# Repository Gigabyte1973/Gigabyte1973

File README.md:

# Gigabyte1973
BMS with RS485 comunication

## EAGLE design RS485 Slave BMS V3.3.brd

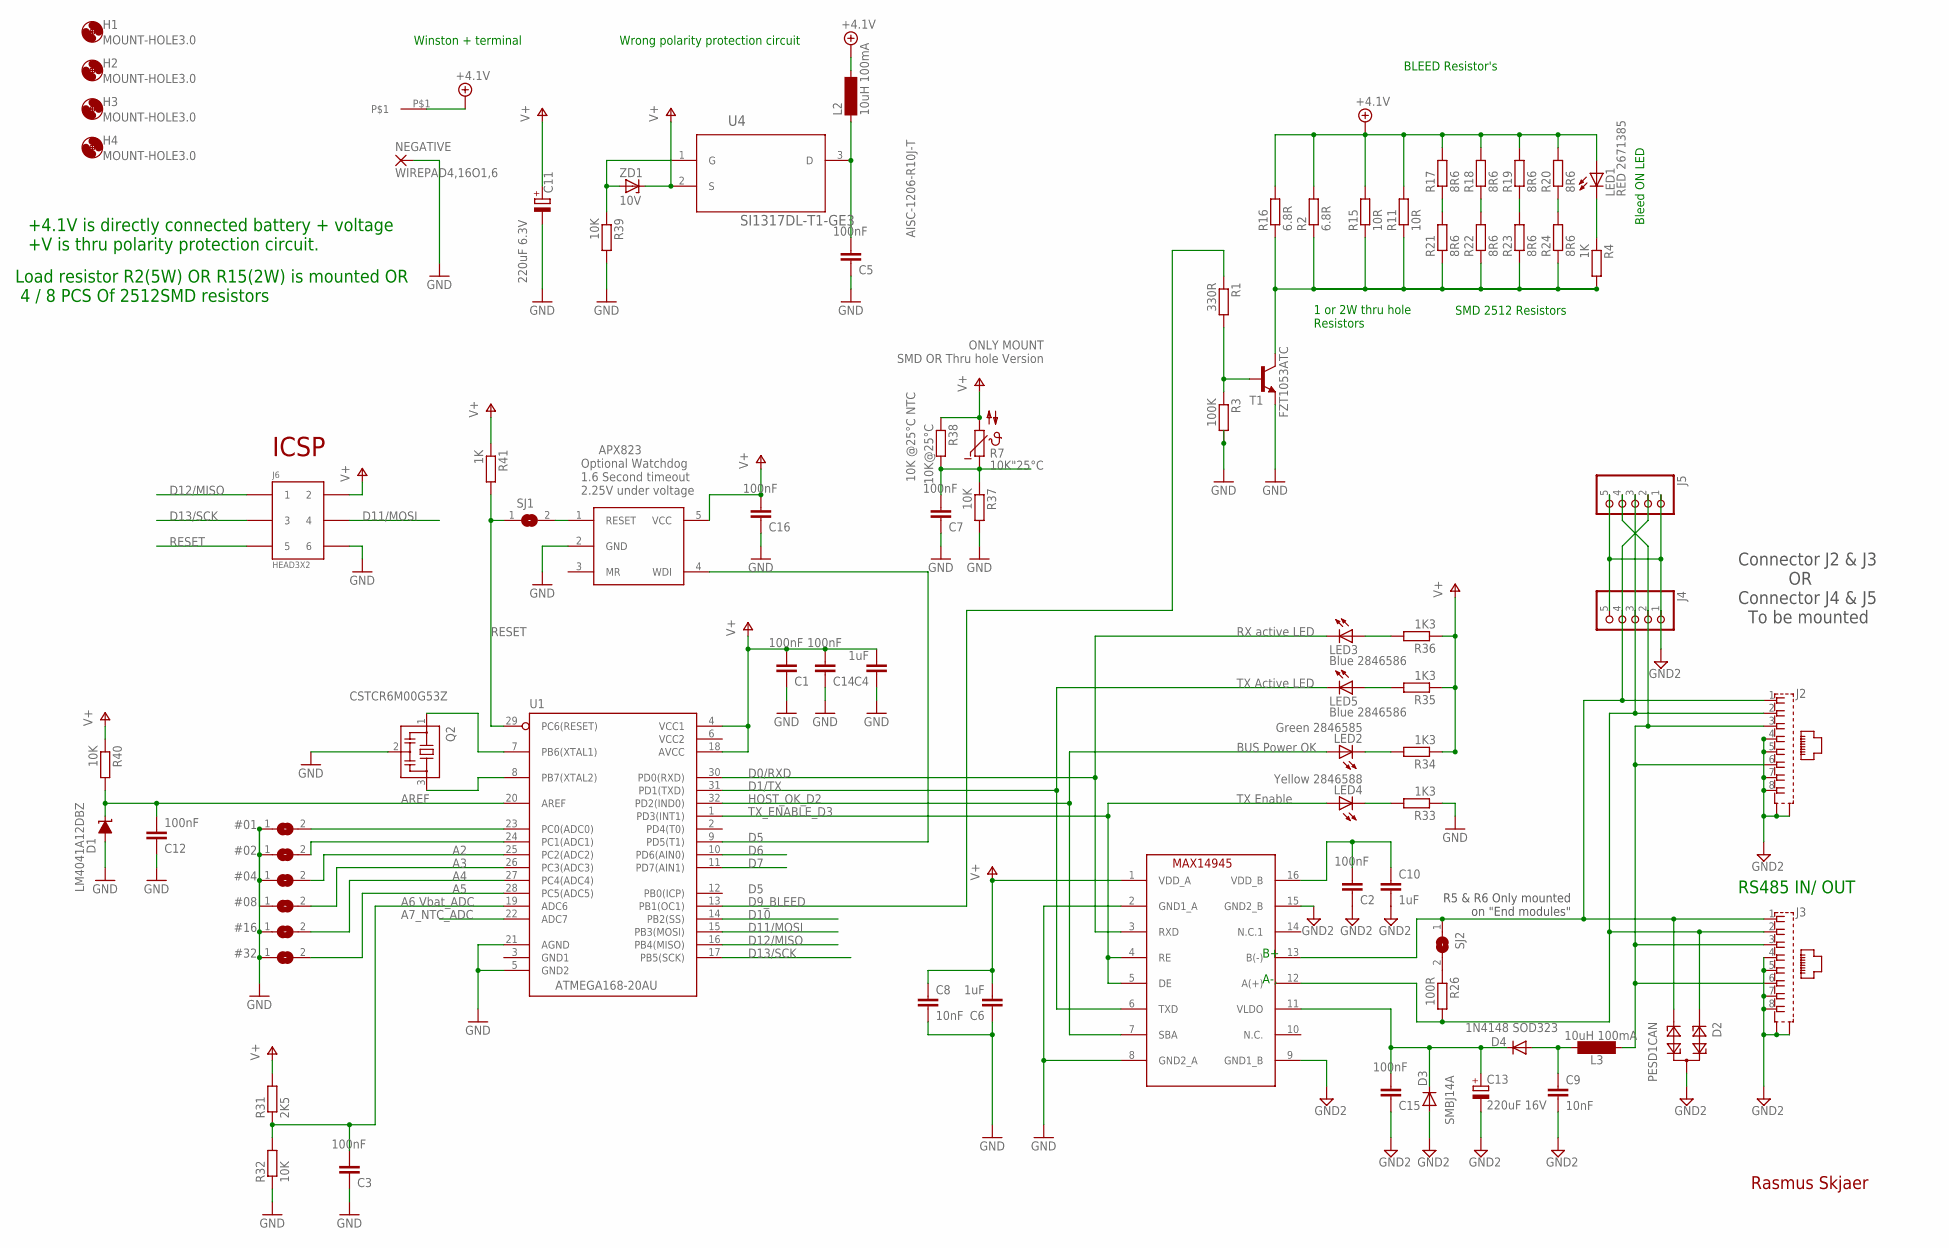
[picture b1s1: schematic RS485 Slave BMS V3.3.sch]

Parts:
#01, #02, #04, #08, #16, #32: SJ
C1, C2, C3, C5, C7, C12, C14, C15, C16: 100nF; C0603
C4, C6: 1uF; C0805
C8, C9: 10nF; C0603
C10: 1uF; C1206
C11: 220uF 6.3V; CT6032
C13: 220uF 16V; D/7343-31R
D1: LM4041A12DBZ; DBZ_R-PDSO-G3
D2: PESD1CAN; SOT23
D3: SMBJ14A; DO214AC
D4: 1N4148 SOD323; SOD323-R
H1, H2, H3, H4: MOUNT-HOLE3.0; 3,0
IC2: MAX14945; SOW16
J2, J3: 555153-1
J4, J5: PINHD-1X5/90; 1X05/90
J6: HEAD3X2
L2, L3: 10uH 100mA; SM-1206
LED1: RED 2671385; CHIP-LED0805
LED2: Green 2846585; CHIP-LED0805
LED3, LED5: Blue 2846586; CHIP-LED0805
LED4: Yellow 2846588; CHIP-LED0805
NEGATIVE: WIREPAD4,16O1,6; 4,16O1,6
Q2: CSTCR6M00G53Z; CSTCR6M
R1: 330R; R0603
R2, R16: 6.8R; V235/17
R3: 100K; R0603
R4, R41: 1K; R0603
R7: 10K"25°C; B57164
R11, R15: 10R; V234/12
R17, R18, R19, R20, R21, R22, R23, R24: 8R6; R2512
R26: 100R; R0805
R31: 2K5; R0603
R32, R37, R39, R40: 10K; R0603
R33, R34, R35, R36: 1K3; R0603
R38: 10K@25°C; R0603
SJ1, SJ2: SJ
T1: FZT1053ATC; SOT223
U1: ATMEGA168-20AU; QFP032
U2: APX823SOT25*; SOT23-5L
U4: SI1317DL-T1-GE3; SOT65P210X110-3N
U$1: WINSTON-160AH-TERMINAL
ZD1: 10V; SOD123

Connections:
+4.1V: L2.2, LED1.A, R2.2, R11.2, R15.2, R16.2, R17.2, R18.2, R19.2, R20.2, U$1.P$1
A2: #04.2, U1.25 (PC2(ADC2))
A3: #08.2, U1.26 (PC3(ADC3))
A4: #16.2, U1.27 (PC4(ADC4))
A5: #32.2, U1.28 (PC5(ADC5))
A6: C3.1, R31.1, R32.2, U1.19 (ADC6)
A7_NTC_ADC: C7.1, R7.1, R37.1, R38.2, U1.22 (ADC7)
A-: D2.1, IC2.12 (A(+)), J2.2, J3.2, J4.3, J5.3, R26.2
AREF: C12.1, D1.1 (C), R40.2, U1.20 (AREF)
B+: D2.2, IC2.13 (B(-)), J2.1, J3.1, J4.4, J5.2, SJ2.1
BLEED: R2.1, R4.2, R11.1, R15.1, R16.1, R21.1, R22.1, R23.1, R24.1, T1.4 (C)
D0/RXD: IC2.3 (RXD), LED3.C, U1.30 (PD0(RXD))
D1/TX: IC2.6 (TXD), LED5.C, U1.31 (PD1(TXD))
D5: U1.9 (PD5(T1)), U2.4 (WDI)
D6: U1.10 (PD6(AIN0))
D7: U1.11 (PD7(AIN1))
D9_BLEED: R1.1, U1.13 (PB1(OC1))
D10: U1.14 (PB2(SS))
D11/MOSI: J6.4, U1.15 (PB3(MOSI))
D12/MISO: J6.1, U1.16 (PB4(MISO))
D13/SCK: J6.3, U1.17 (PB5(SCK))
DCIN: J2.3, J2.6, J3.3, J3.6, J4.2, J5.4, L3.2
GND: #01.1, #02.1, #04.1, #08.1, #16.1, #32.1, C1.2, C3.2, C4.1, C5.2, C6.1, C7.2, C8.2, C11.-, C12.2, C14.2, C16.2, D1.2 (A), IC2.2 (GND1_A), IC2.8 (GND2_A), J6.6, NEGATIVE.1, Q2.2, R3.2, R32.1, R33.1, R37.2, R39.2, T1.3 (E), U1.5 (GND2), U1.21 (AGND), U2.2 (GND)
GND1: U1.3 (GND1)
GND2: C2.2, C9.2, C10.2, C13.-, C15.2, D2.3, D3.A, IC2.9 (GND1_B), IC2.15 (GND2_B), J2.4, J2.5, J2.7, J2.8, J2.G1 (S1), J2.G2 (S2), J3.4, J3.5, J3.7, J3.8, J3.G1 (S1), J3.G2 (S2), J4.1, J4.5, J5.1, J5.5
HOST_OK_D2: IC2.7 (SBA), LED2.A, U1.32 (PD2(IND0))
unnamed: R1.2, R3.1, T1.1 (B)
unnamed: #02.2, U1.24 (PC1(ADC1))
unnamed: LED4.C, R33.2
unnamed: LED3.A, R36.2
unnamed: R39.1, U4.1 (G), ZD1.A
unnamed: LED5.A, R35.2
unnamed: C5.1, L2.1, U4.3 (D)
unnamed: #01.2, U1.23 (PC0(ADC0))
unnamed: LED2.C, R34.2
unnamed: LED1.C, R4.1
unnamed: SJ1.2, U2.1 (RESET)
unnamed: C9.1, D4.A, L3.1
unnamed: R26.1, SJ2.2
unnamed: R20.1, R24.2
unnamed: R19.1, R23.2
unnamed: R18.1, R22.2
unnamed: R17.1, R21.2
unnamed: Q2.1, U1.7 (PB6(XTAL1))
unnamed: Q2.3, U1.8 (PB7(XTAL2))
RESET: J6.5, R41.2, SJ1.1, U1.29 (PC6(RESET))
TX_ENABLE_D3: IC2.4 (RE), IC2.5 (DE), LED4.A, U1.1 (PD3(INT1))
V+: C1.1, C4.2, C6.2, C8.1, C11.+, C14.1, C16.1, IC2.1 (VDD_A), J6.2, R7.2, R31.2, R34.1, R35.1, R36.1, R38.1, R40.1, R41.1, U1.4 (VCC1), U1.18 (AVCC), U2.5 (VCC), U4.2 (S), ZD1.C
VCC2: U1.6 (VCC2)
VCC2_FILTER: C13.+, C15.1, D3.C, D4.C, IC2.11 (VLDO)
VDD_B: C2.1, C10.1, IC2.16 (VDD_B)

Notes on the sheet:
BLEED Resistor's
Bleed ON LED
Wrong polarity protection circuit
+4.1V is directly connected battery + voltage +V is thru polarity protection circuit.
Load resistor R2(5W) OR R15(2W) is mounted OR 4 / 8 PCS Of 2512SMD resistors
Winston + terminal
SMD 2512 Resistors
1 or 2W thru hole Resistors
RX active LED
TX Enable
TX Active LED
10K @25°C NTC
Rasmus Skjaer
RS485 IN/ OUT
R5 & R6 Only mounted on "End modules"
Connector J2 & J3 OR Connector J4 & J5 To be mounted
AISC-1206-R10J-T
ONLY MOUNT SMD OR Thru hole Version
A-,
ICSP
APX823 Optional Watchdog 1.6 Second timeout 2.25V under voltage
BUS Power OK
A6 Vbat_ADC

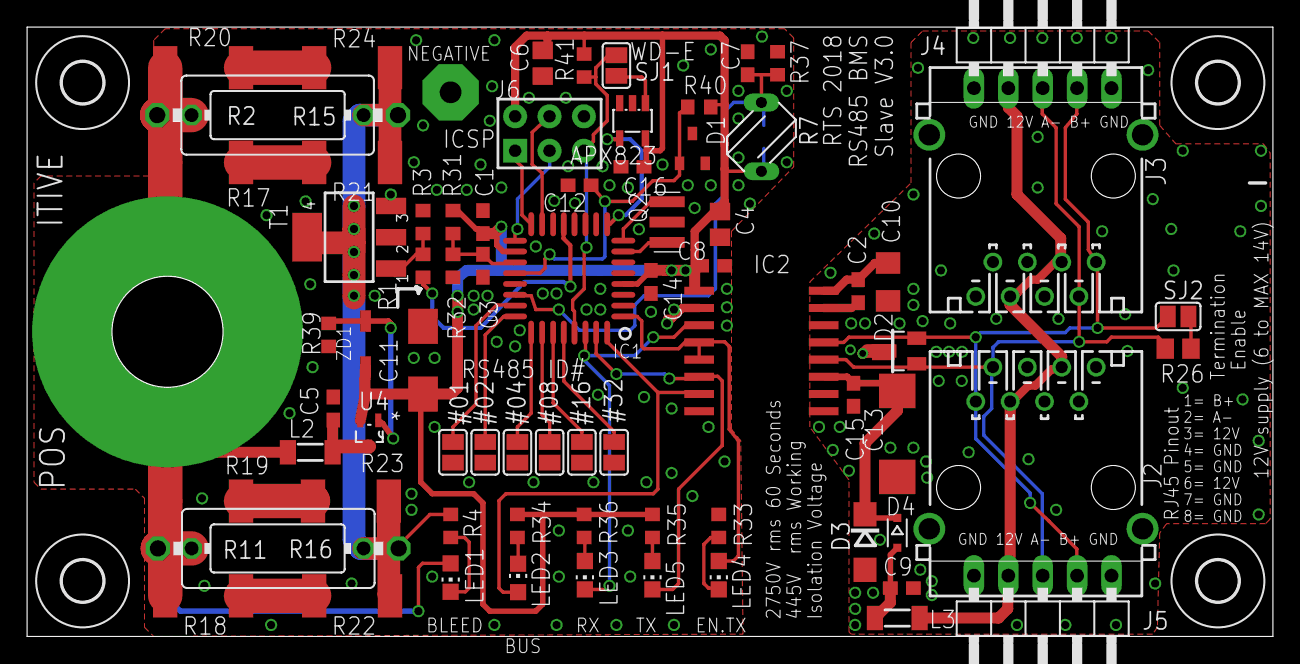
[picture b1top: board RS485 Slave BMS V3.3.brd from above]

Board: 2 copper layers, 92.0 x 45.0 mm, 82 parts (1 on the bottom side), 46 nets.

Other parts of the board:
U$2: A4L-LOC

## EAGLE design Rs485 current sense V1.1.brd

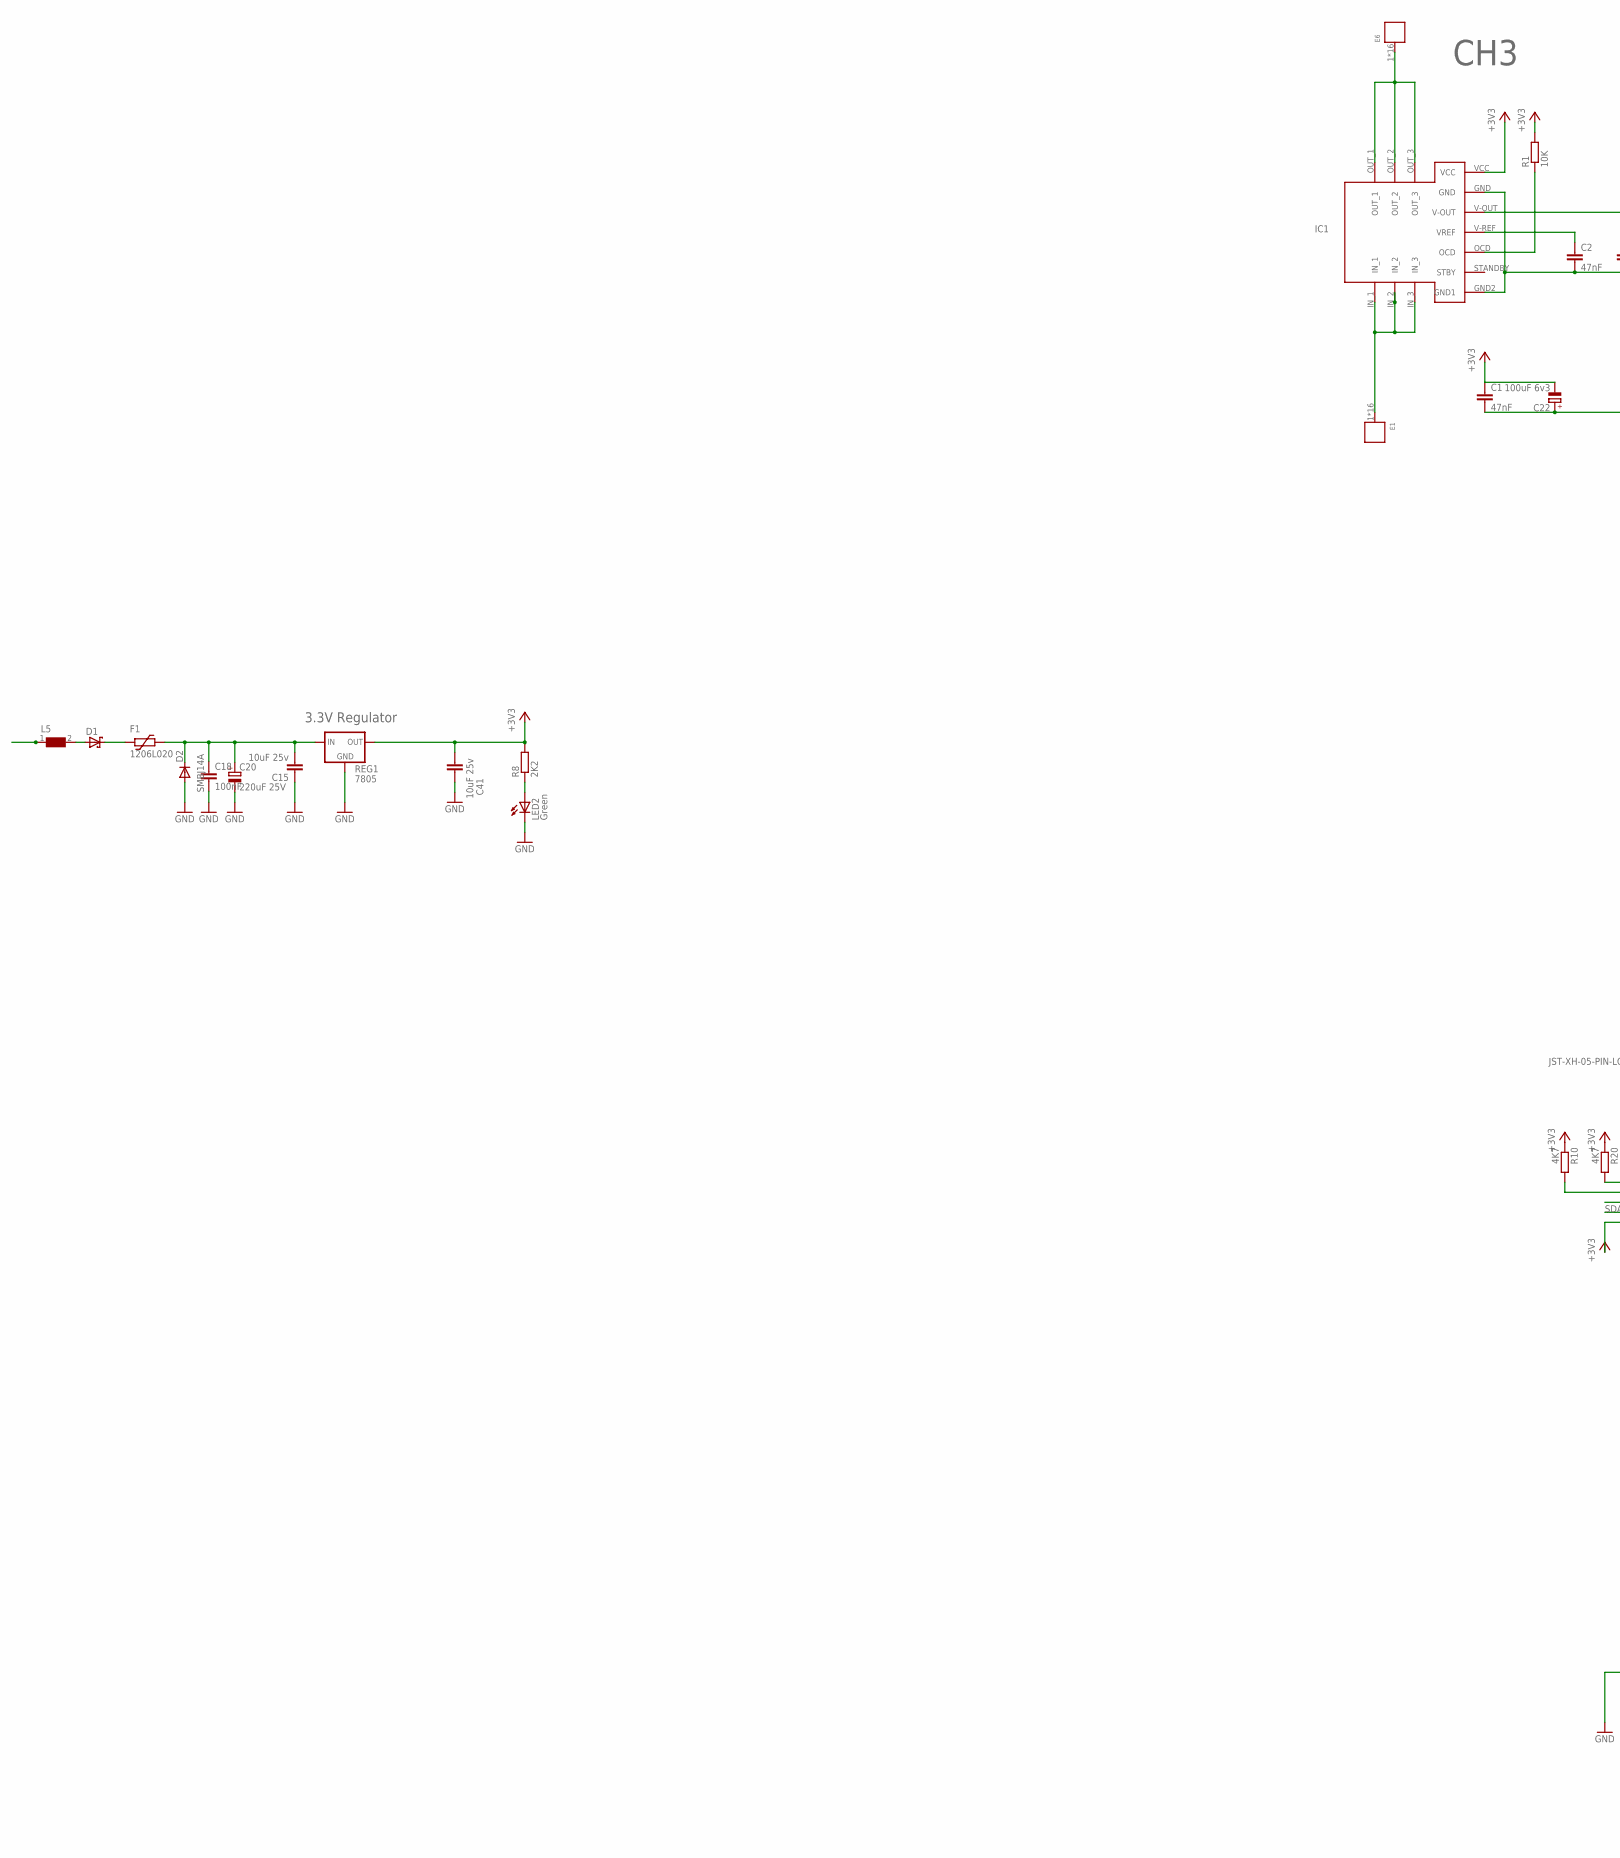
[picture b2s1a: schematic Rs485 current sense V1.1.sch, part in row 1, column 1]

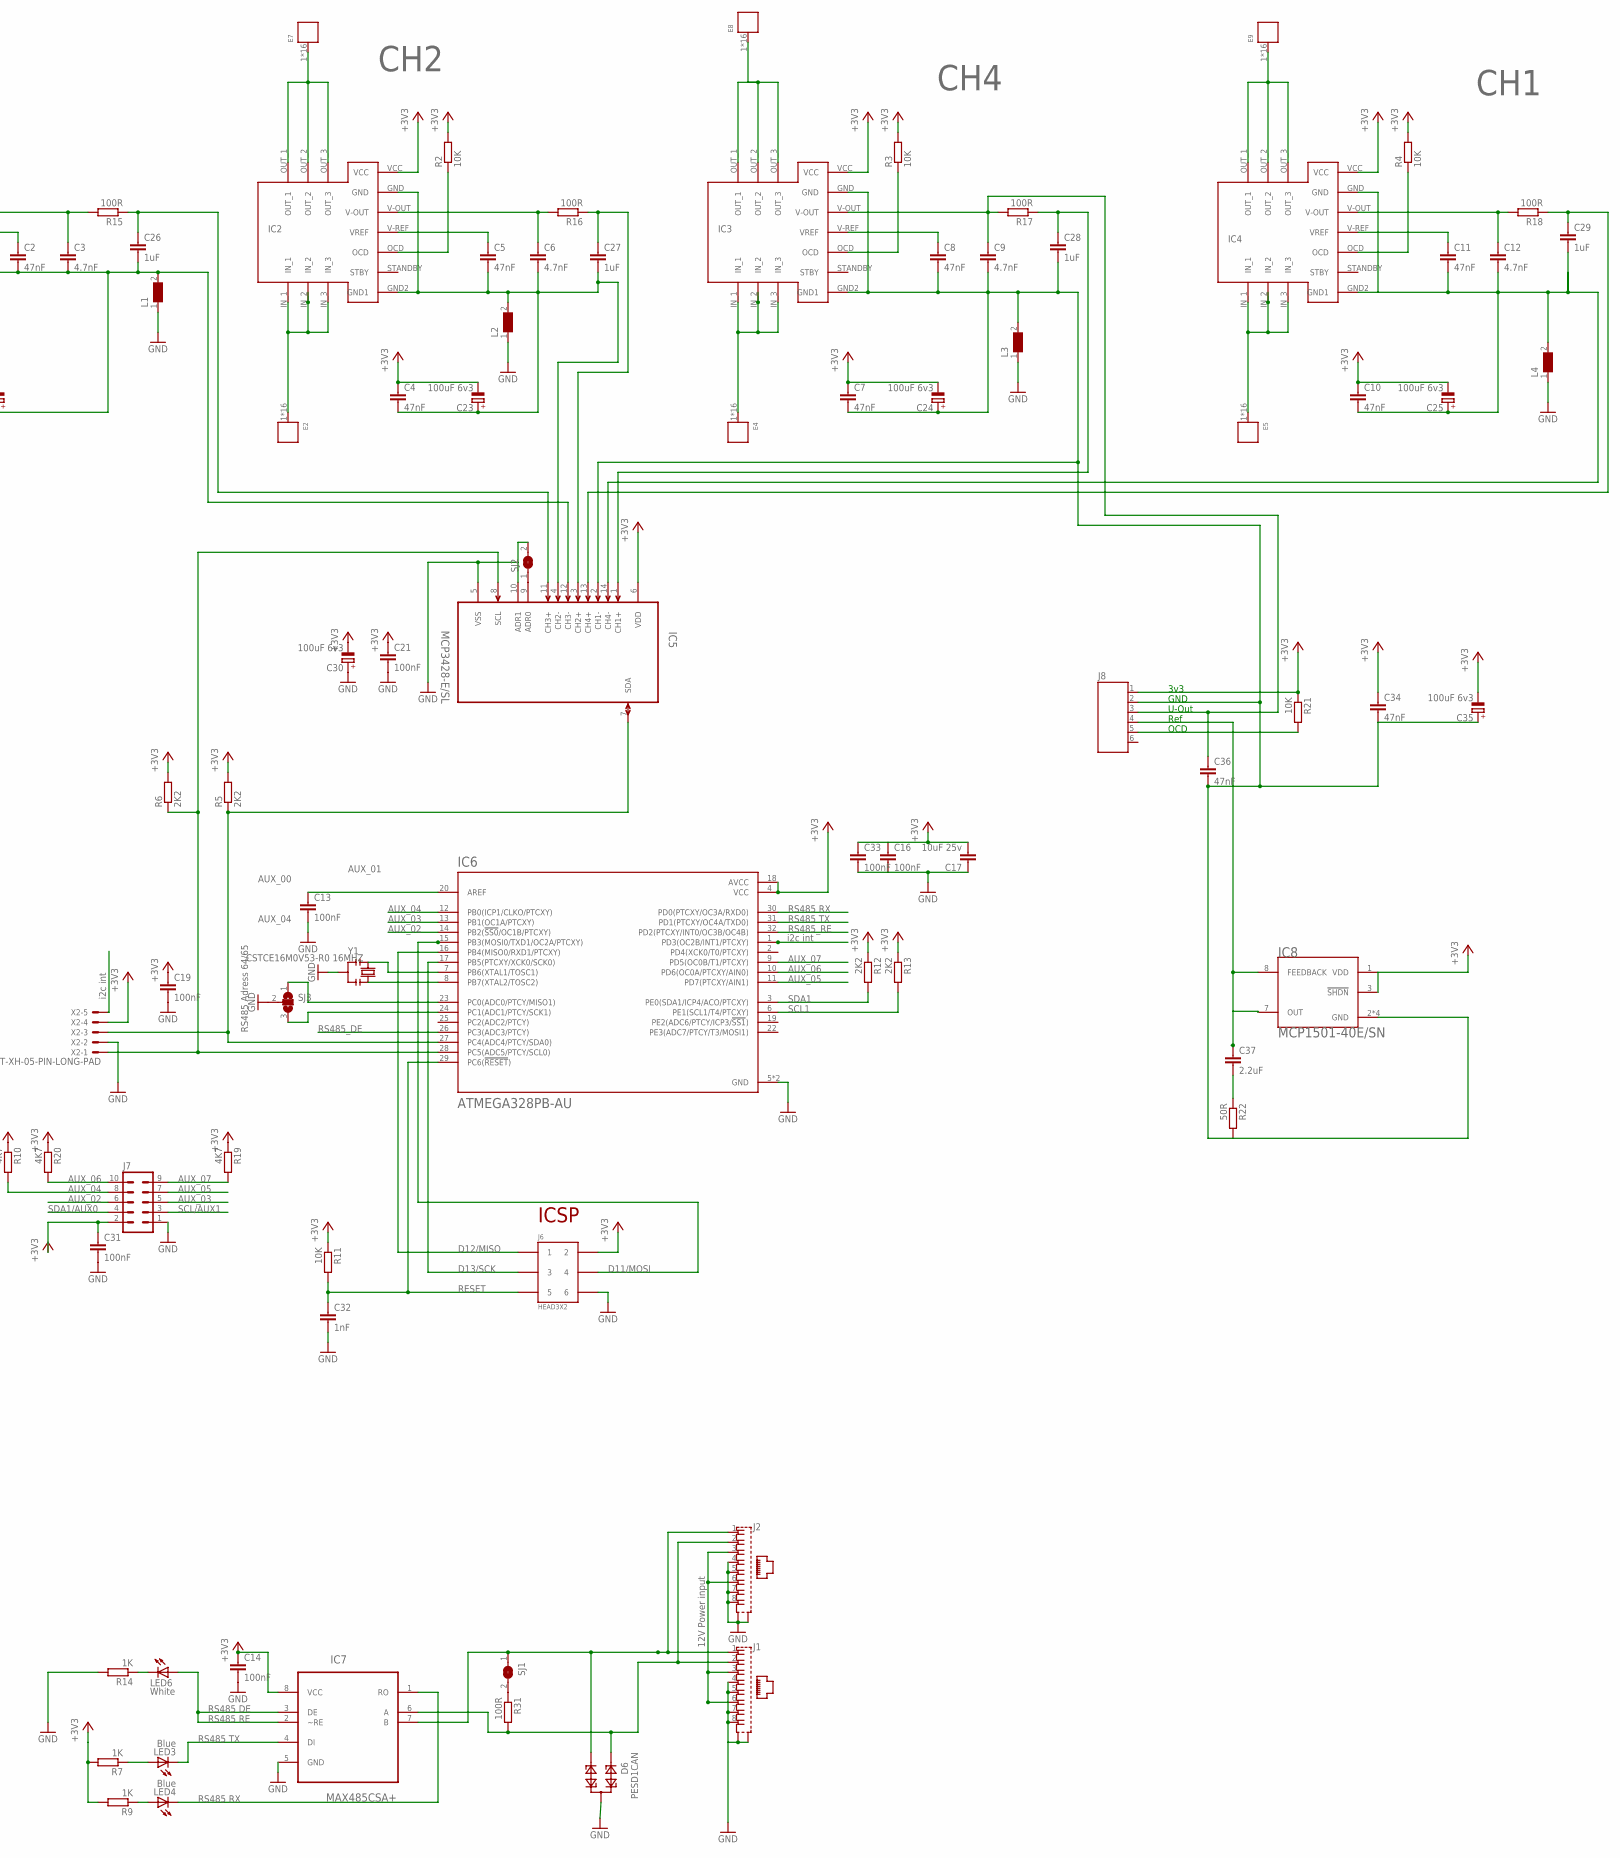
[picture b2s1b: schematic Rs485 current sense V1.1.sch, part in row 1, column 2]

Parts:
C1, C2, C4, C5, C7, C8, C10, C11, C34, C36: 47nF; C0603
C3, C6, C9, C12: 4.7nF; C0603
C13, C14, C16, C18, C19, C21, C31, C33: 100nF; C0603
C15, C17, C41: 10uF 25v; C1206
C20: 220uF 25V; PANASONIC_F
C22, C23, C24, C25, C30, C35: 100uF 6v3; CT3528
C26, C27, C28, C29: 1uF; C0603
C32: 1nF; C0603
C37: 2.2uF; C0805
D1: SCHOTTKY-DIODESMD; SMB
D2: SMBJ14A; DO214AC
D6: PESD1CAN; SOT23
E1, E2, E4, E5, E6, E7, E8, E9: WP-BUFU_J(10); 16PINS_10X10_FULL
F1: 1206L020; 1206L
IC1, IC2, IC3, IC4: HO15-NP/SP33-1000
IC5: MCP3428-E/SL; SOIC127P600X175-14N
IC6: ATMEGA328PB-AU; QFP80P900X900X120-32N
IC7: MAX485CSA+; SOIC127P600X175-8N
IC8: MCP1501-40E/SN; SOIC127P600X175-8N
J1, J2: 555153-1
J6: HEAD3X2
J7: MA05-2
J8: JST-PH6
L1, L2, L3, L4: WE-CBF-74279209_0805; 0805
L5: WE-CBF-7427922_1206; 1206
LED2: Green; CHIPLED_0805
LED3, LED4: Blue; CHIPLED_0805
LED6: White; CHIPLED_0805
R1, R2, R3, R4, R11, R21: 10K; R0603
R5, R6, R12, R13: 2K2; R0603
R7, R9, R14: 1K; R0805
R8: 2K2; R0805
R10, R19, R20: 4K7; R0603
R15, R16, R17, R18: 100R; R0603
R22: 50R; R0603
R31: 100R; R0805
REG1: 7805; 78XXS
SJ1, SJ2: SJ
SJ3: SJ2W; SJ_2
X2: JST-XH-05-PIN-LONG-PAD; JST-XH-05-PACKAGE-LONG-PAD
Y1: CSTCE16M0V53-R0 16MHZ; RESONATOR

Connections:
1GNDA: C10.2, C11.2, C12.2, C25.- (+), C29.2, IC4.GND, IC4.GND2 (GND1), IC5.14 (CH4-), L4.2
1_IN: E5.1, E5.2, E5.3, E5.4, E5.5, E5.6, E5.7, E5.8, E5.9, E5.10, E5.11, E5.12, E5.13, E5.14, E5.15, E5.16, IC4.IN_1, IC4.IN_2, IC4.IN_3
1_OUT: E9.1, E9.2, E9.3, E9.4, E9.5, E9.6, E9.7, E9.8, E9.9, E9.10, E9.11, E9.12, E9.13, E9.14, E9.15, E9.16, IC4.OUT_1, IC4.OUT_2, IC4.OUT_3
2GND: C4.2, C5.2, C6.2, C23.- (+), C27.2, IC2.GND, IC2.GND2 (GND1), IC5.4 (CH2-), L2.2
2_IN: E2.1, E2.2, E2.3, E2.4, E2.5, E2.6, E2.7, E2.8, E2.9, E2.10, E2.11, E2.12, E2.13, E2.14, E2.15, E2.16, IC2.IN_1, IC2.IN_2, IC2.IN_3
2_OUT: E7.1, E7.2, E7.3, E7.4, E7.5, E7.6, E7.7, E7.8, E7.9, E7.10, E7.11, E7.12, E7.13, E7.14, E7.15, E7.16, IC2.OUT_1, IC2.OUT_2, IC2.OUT_3
3GND: C1.2, C2.2, C3.2, C22.- (+), C26.2, IC1.GND, IC1.GND2 (GND1), IC5.12 (CH3-), L1.2
3_IN: E1.1, E1.2, E1.3, E1.4, E1.5, E1.6, E1.7, E1.8, E1.9, E1.10, E1.11, E1.12, E1.13, E1.14, E1.15, E1.16, IC1.IN_1, IC1.IN_2, IC1.IN_3
3_OUT: E6.1, E6.2, E6.3, E6.4, E6.5, E6.6, E6.7, E6.8, E6.9, E6.10, E6.11, E6.12, E6.13, E6.14, E6.15, E6.16, IC1.OUT_1, IC1.OUT_2, IC1.OUT_3
4GNDA: C7.2, C8.2, C9.2, C24.- (+), C28.2, C34.2, C35.- (+), C36.2, IC3.GND, IC3.GND2 (GND1), IC5.2 (CH1-), IC8.2 (GND), IC8.4 (GND), IC8.5 (GND), IC8.6 (GND), J8.2, L3.2, R22.2
4_IN: E4.1, E4.2, E4.3, E4.4, E4.5, E4.6, E4.7, E4.8, E4.9, E4.10, E4.11, E4.12, E4.13, E4.14, E4.15, E4.16, IC3.IN_1, IC3.IN_2, IC3.IN_3
4_OUT: E8.1, E8.2, E8.3, E8.4, E8.5, E8.6, E8.7, E8.8, E8.9, E8.10, E8.11, E8.12, E8.13, E8.14, E8.15, E8.16, IC3.OUT_1, IC3.OUT_2, IC3.OUT_3
12V: J1.3, J1.6, J2.3, J2.6, L5.1
+3V3: C1.1, C4.1, C7.1, C10.1, C14.1, C16.1, C17.2, C19.1, C21.1, C22.+ (-), C23.+ (-), C24.+ (-), C25.+ (-), C30.+ (-), C31.1, C33.1, C34.1, C35.+ (-), C41.2, IC1.VCC, IC2.VCC, IC3.VCC, IC4.VCC, IC5.6 (VDD), IC6.4 (VCC), IC6.18 (AVCC), IC7.8 (VCC), IC8.1 (VDD), IC8.3 (!SHDN), J6.2, J7.2, J8.1, R1.2, R2.2, R3.2, R4.2, R5.2, R6.2, R7.2, R8.2, R9.2, R10.1, R11.1, R12.1, R13.1, R19.1, R20.1, R21.1, REG1.OUT, X2.4
ATMEGA-AREF: C13.1, IC6.20 (AREF)
AUX_02: IC6.14 (PB2(!SS0!/OC1B/PTCXY)), J7.6
AUX_03: IC6.13 (PB1(OC1A/PTCXY)), J7.5
AUX_04: IC6.12 (PB0(ICP1/CLKO/PTCXY)), J7.8, R10.2
AUX_05: IC6.11 (PD7(PTCXY/AIN1)), J7.7
AUX_06: IC6.10 (PD6(OC0A/PTCXY/AIN0)), J7.10, R20.2
AUX_07: IC6.9 (PD5(OC0B/T1/PTCXY)), J7.9, R19.2
CH1-OUTA: C29.1, IC5.13 (CH4+), R18.1
CH2-OUT: C27.1, IC5.3 (CH2+), R16.1
CH3-OUT: C26.1, IC5.11 (CH3+), R15.1
CH4-OUTA: C28.1, IC5.1 (CH1+), R17.1
D11/MOSI: IC6.15 (PB3(MOSI0/TXD1/OC2A/PTCXY)), J6.4
D12/MISO: IC6.16 (PB4(MISO0/RXD1/PTCXY)), J6.1
D13/SCK: IC6.17 (PB5(PTCXY/XCK0/SCK0)), J6.3
GND: C13.2, C14.2, C15.1, C16.2, C17.1, C18.2, C19.2, C20.-, C21.2, C30.- (+), C31.2, C32.2, C33.2, C41.1, D2.A, D6.3, IC5.5 (VSS), IC5.10 (ADR1), IC6.5 (GND), IC6.21 (GND), IC7.5 (GND), J1.4, J1.5, J1.7, J1.8, J1.G1 (S1), J1.G2 (S2), J2.4, J2.5, J2.7, J2.8, J2.G1 (S1), J2.G2 (S2), J6.6, J7.1, L1.1, L2.1, L3.1, L4.1, LED2.C, R14.2, REG1.GND, SJ2.2, SJ3.2, X2.2, Y1.2
I2C_INT: IC6.1 (PD3(OC2B/INT1/PTCXY)), X2.5
I2C_SCL: IC5.8 (SCL), IC6.28 (PC5(ADC5/PTCY/SCL0)), R6.1, X2.1
I2C_SDA: IC5.7 (SDA), IC6.27 (PC4(ADC4/PTCY/SDA0)), R5.1, X2.3
unnamed: IC6.23 (PC0(ADC0/PTCY/MISO1)), SJ3.1
unnamed: IC1.OCD, R1.1
unnamed: IC6.24 (PC1(ADC1/PTCY/SCK1)), SJ3.3
unnamed: C2.1, IC1.V-REF (VREF)
unnamed: J8.5, R21.2
unnamed: C9.1, C36.1, IC3.V-OUT, J8.3, R17.2
unnamed: C37.1, IC8.7 (OUT), IC8.8 (FEEDBACK), J8.4
unnamed: IC2.OCD, R2.1
unnamed: C5.1, IC2.V-REF (VREF)
unnamed: C6.1, IC2.V-OUT, R16.2
unnamed: C37.2, R22.1
unnamed: D1.A, L5.2
unnamed: IC3.OCD, R3.1
unnamed: C8.1, IC3.V-REF (VREF)
unnamed: IC4.OCD, R4.1
unnamed: C11.1, IC4.V-REF (VREF)
unnamed: IC6.8 (PB7(XTAL2/TOSC2)), Y1.3
unnamed: LED2.A, R8.1
unnamed: D1.C, F1.2
unnamed: LED3.A, R7.1
unnamed: LED4.A, R9.1
unnamed: LED6.C, R14.1
unnamed: IC5.9 (ADR0), SJ2.1
unnamed: C3.1, IC1.V-OUT, R15.2
unnamed: C12.1, IC4.V-OUT, R18.2
unnamed: R31.1, SJ1.2
RESET: C32.1, IC6.29 (PC6(!RESET!)), J6.5, R11.2
RS485_DE: IC6.26 (PC3(ADC3/PTCY)), IC7.2 (~RE), IC7.3 (DE), LED6.A
RS485_N: D6.1, IC7.6 (A), J1.2, J2.2, R31.2
RS485_P: D6.2, IC7.7 (B), J1.1, J2.1, SJ1.1
RS485_RE: IC6.32 (PD2(PTCXY/INT0/OC3B/OC4B))
RS485_RX: IC6.30 (PD0(PTCXY/OC3A/RXD0)), IC7.1 (RO), LED4.C
RS485_TX: IC6.31 (PD1(PTCXY/OC4A/TXD0)), IC7.4 (DI), LED3.C
SCL1: IC6.6 (PE1(SCL1/T4/PTCXY)), J7.3, R13.2
SDA1: IC6.3 (PE0(SDA1/ICP4/ACO/PTCXY)), J7.4, R12.2
VBAT12V: C15.2, C18.1, C20.+, D2.C, F1.1, REG1.IN
XTAL2: IC6.7 (PB6(XTAL1/TOSC1)), Y1.1

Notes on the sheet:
RS485 TX
RS485 RX
RS485 RE
RS485 DE
3.3V Regulator
IC1
IC2
IC3
IC4
ICSP
RS485_RE
RS485_DE
AUX_06
AUX_07
AUX_05
AUX_03
AUX_04
AUX_02
AUX_01
AUX_00
SCL1
SDA1
SDA1/AUX0
SCL/AUX1
RS485 Adress 64/65
3v3
GND
Ref
U-Out
OCD
CH4
CH1
CH2
CH3
i2c int
12V Power input

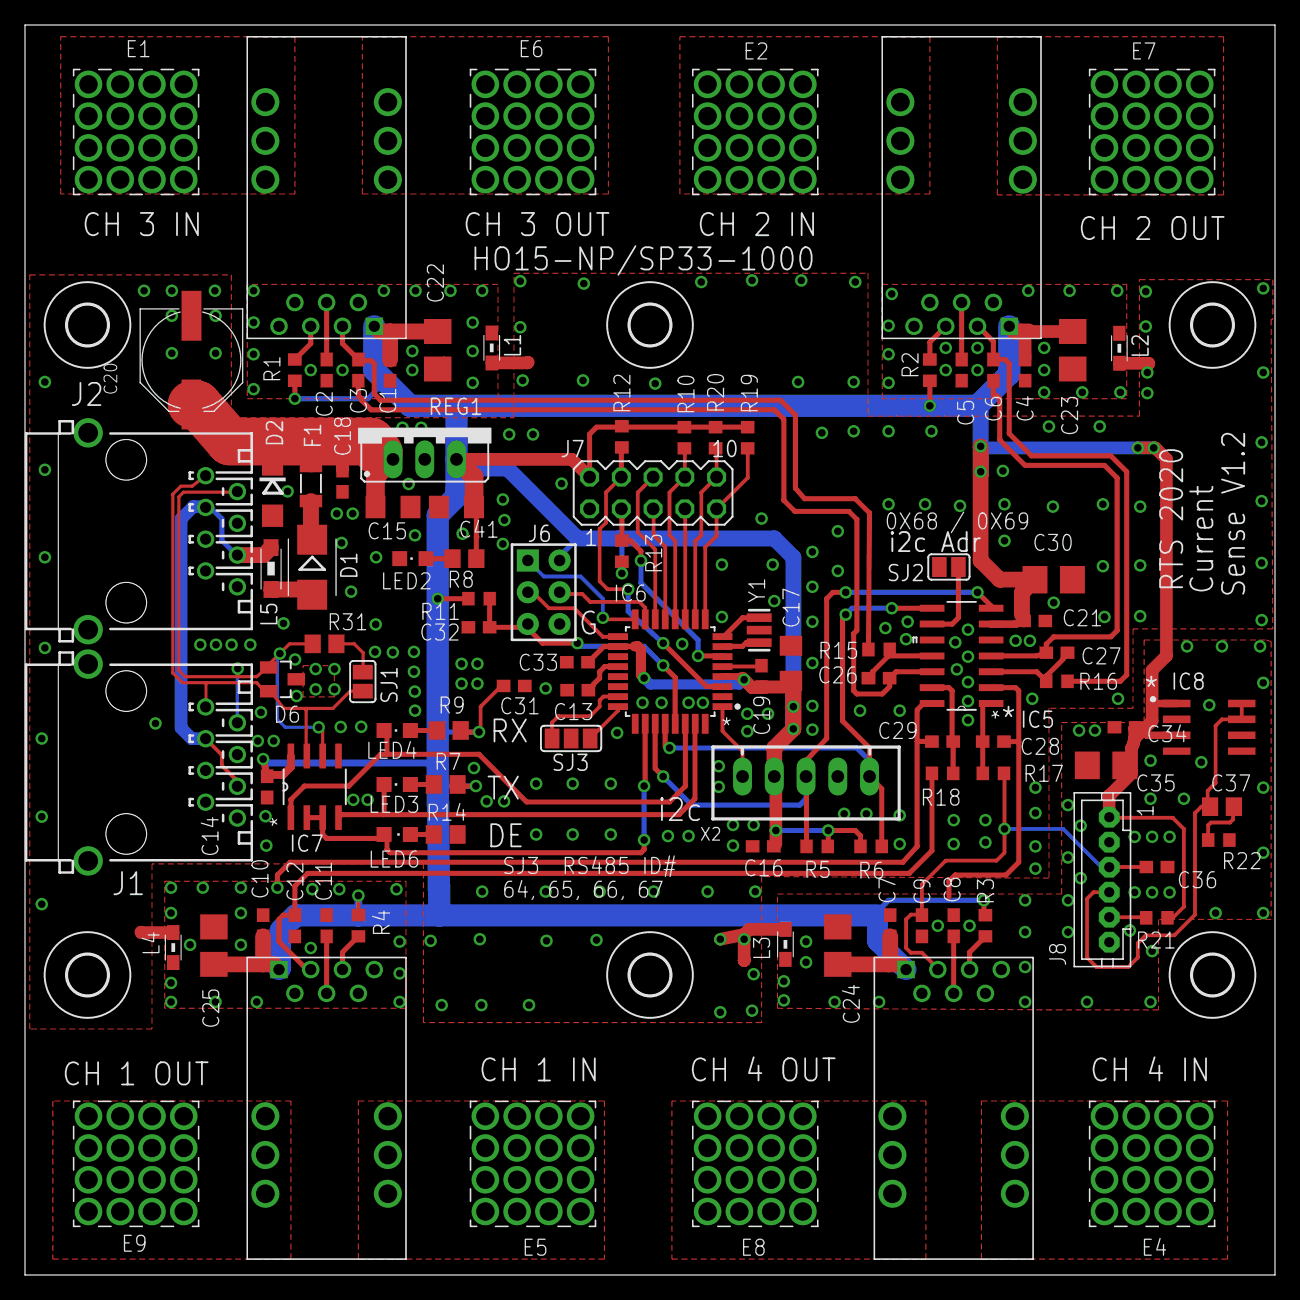
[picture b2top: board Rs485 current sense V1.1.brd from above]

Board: 2 copper layers, 100.0 x 100.0 mm, 107 parts (0 on the bottom side), 68 nets.

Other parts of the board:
U$2, U$3, U$4, U$5, U$6, U$7: 3,2

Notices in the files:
parts and their libraries:
Wurth_Elektronik_Electromechanic_Power_E: Copyright: Würth Elektronik
